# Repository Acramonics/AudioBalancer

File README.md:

AudioBalancer
=============

Andrew Martin, acramonics, 2026
-------------------------------

`AudioBalancer` is a balanced line receiver to unbalanced and an
unbalanced to balanced driver on a single board. This could be used as
a standalone device or as an add on to another circuit - the board has
been designed to be as small as possible while using through-hole
components.

A -15V/0/+15V power supply is needed.

The circuit uses the SSM2141P receiver and SSM2142P receiver. These
are now end-of-life, but still quite easy to find quite cheaply.

Both receiver and driver contain capacitors for decoupling 48V phantom
power on the balanced connection protection for the chips if these are
charged and the inputs are accidentally shorted to earth. See the
[Phantom Menace](./docs/AES5335_48V_Phantom_Menace.pdf) document.

|    | Components               | Value | Function            | Options              |
| :- | :----------------------- | :---- | :------------------ | :------------------- |
| 1  | C3,C4,C13,C14            | 10nF  | HF coupling         | Omit if not needed   |
| 2  | C1,C2,C11,C12            | 47uF  | Phantom protection  | Bridge if not needed |
| 3  | D1,D2,D3,D4,D5,D6,D7,D8  | SB160 | Short protection    | Omit if not needed   |
| 4  | R4,R5,R6,R7              | 10K   | Short protection    | Omit if not needed   |

1. The 10nF capacitors across the decoupling capacitors are to ensure
   a good high frequency response. Depending on your application these
   may not be needed.

2. These prevent the 48V phantom power reaching the ICs. If you are
   confident that this is not a problem in your application, they may
   be bridged out.

3. If the 47uF capacitors are charged by phantom power and the signal
   pins are accidentally shorted to ground these provide protection to
   the chips by shunting the voltage to the power rail. Normal 1N4148
   diodes may also be used, but they will not provide the same degree
   of protection.

4. These allow the 47uF capacitors to discharge in the event of a short.

Consequently, if you are confident of no problems with phantom power,
you can omit the eight Schottky diodes, and the four 10K resistors and
replace the four 47uF coupling capacitors with links.

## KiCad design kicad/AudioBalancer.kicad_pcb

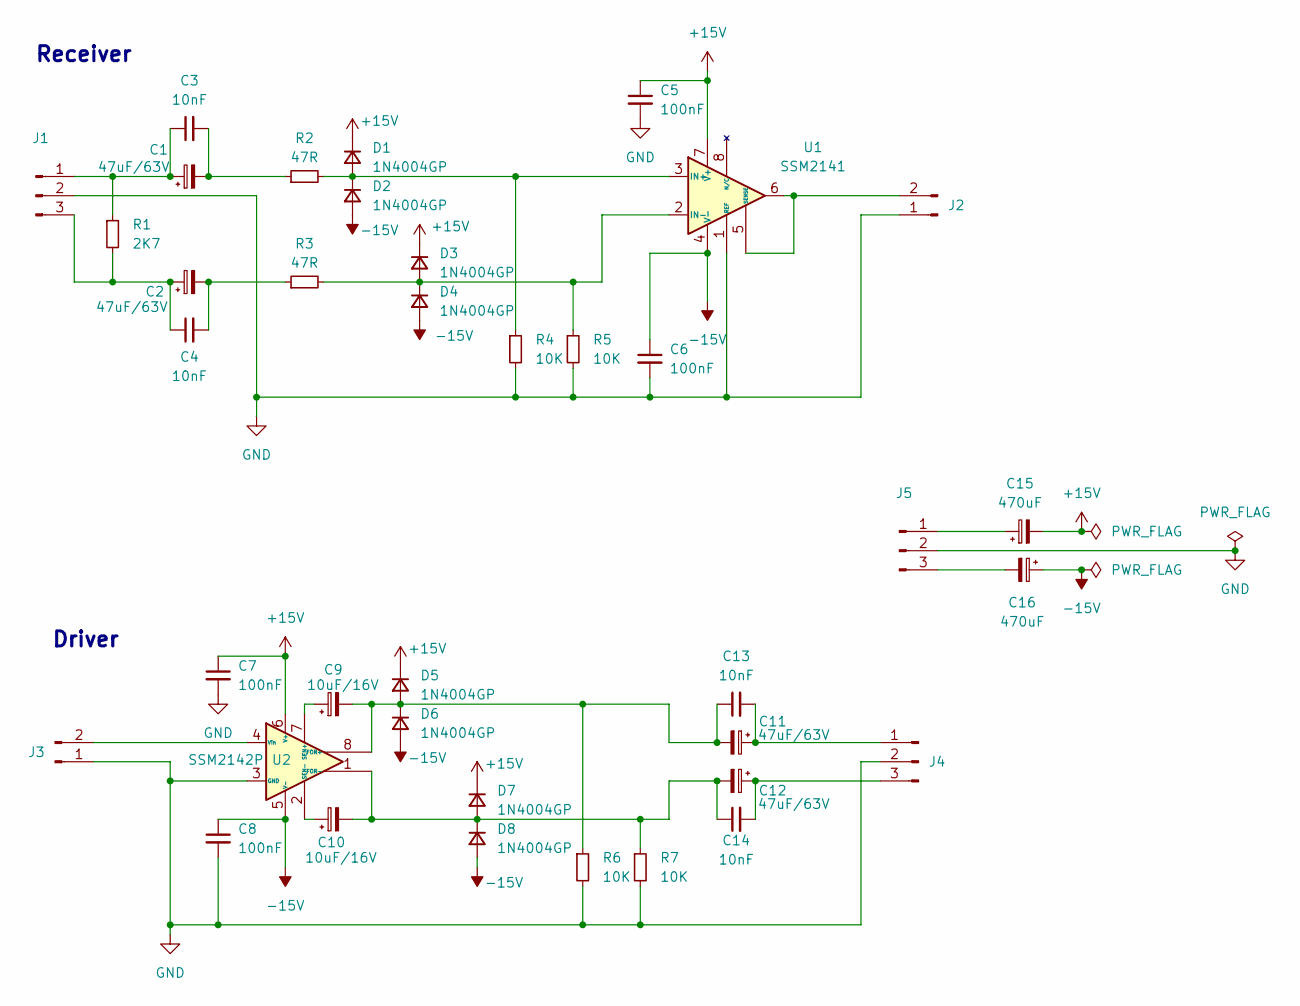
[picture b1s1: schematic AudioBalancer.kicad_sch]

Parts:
C1, C2, C11, C12: 47uF/63V; CP_Radial_D10.0mm_P5.00mm
C3, C4, C13, C14: 10nF; C_Rect_L7.0mm_W2.0mm_P5.00mm
C5, C6, C7, C8: 100nF; C_Rect_L7.0mm_W2.5mm_P5.00mm
C9, C10: 10uF/16V; CP_Radial_D5.0mm_P2.00mm
C15, C16: 470uF; CP_Radial_D10.0mm_P5.00mm_P7.50mm
D1, D2, D3, D4, D5, D6, D7, D8: 1N4004GP; D_DO-41_SOD81_P10.16mm_Horizontal
J1, J4, J5: Conn_01x03_Pin; Molex_KK-254_AE-6410-03A_1x03_P2.54mm_Vertical
J2, J3: Conn_01x02_Pin; Molex_KK-254_AE-6410-02A_1x02_P2.54mm_Vertical
R1: 2K7; R_Axial_DIN0207_L6.3mm_D2.5mm_P10.16mm_Horizontal
R2, R3: 47R; R_Axial_DIN0207_L6.3mm_D2.5mm_P10.16mm_Horizontal
R4, R5, R6, R7: 10K; R_Axial_DIN0207_L6.3mm_D2.5mm_P10.16mm_Horizontal
U1: SSM2141; DIP-8_W7.62mm
U2: SSM2142P; DIP-8_W7.62mm

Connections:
+15V: C5.1, C7.1, C15.2, D1.1 (K), D3.1 (K), D5.1 (K), D7.1 (K), U1.7 (V+), U2.6 (V+)
-15V: C6.1, C8.1, C16.1, D2.2 (A), D4.2 (A), D6.2 (A), D8.2 (A), U1.4 (V-), U2.5 (V-)
GND: C5.2, C6.2, C7.2, C8.2, J1.2, J2.1, J3.1, J4.2, J5.2, R4.2, R5.2, R6.2, R7.2, U1.1 (REF), U2.3 (GND)
unnamed: C1.2, C3.2, R2.1
unnamed: C2.2, C4.2, R3.1
unnamed: D1.2 (A), D2.1 (K), R2.2, R4.1, U1.3 (IN+)
unnamed: D3.2 (A), D4.1 (K), R3.2, R5.1, U1.2 (IN-)
unnamed: C9.2, C11.2, C13.1, D5.2 (A), D6.1 (K), R6.1, U2.8 (FOR+)
unnamed: C10.2, C12.2, C14.1, D7.2 (A), D8.1 (K), R7.1, U2.1 (FOR-)
unnamed: C1.1, C3.1, J1.1, R1.1
unnamed: C2.1, C4.1, J1.3, R1.2
unnamed: J2.2, U1.5 (SENSE), U1.6
unnamed: J3.2, U2.4 (Vin)
unnamed: C11.1, C13.2, J4.1
unnamed: C12.1, C14.2, J4.3
unnamed: C15.1, J5.1
unnamed: C16.2, J5.3
unnamed: C9.1, U2.7 (SEN+)
unnamed: C10.1, U2.2 (SEN-)

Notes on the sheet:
Receiver
Driver

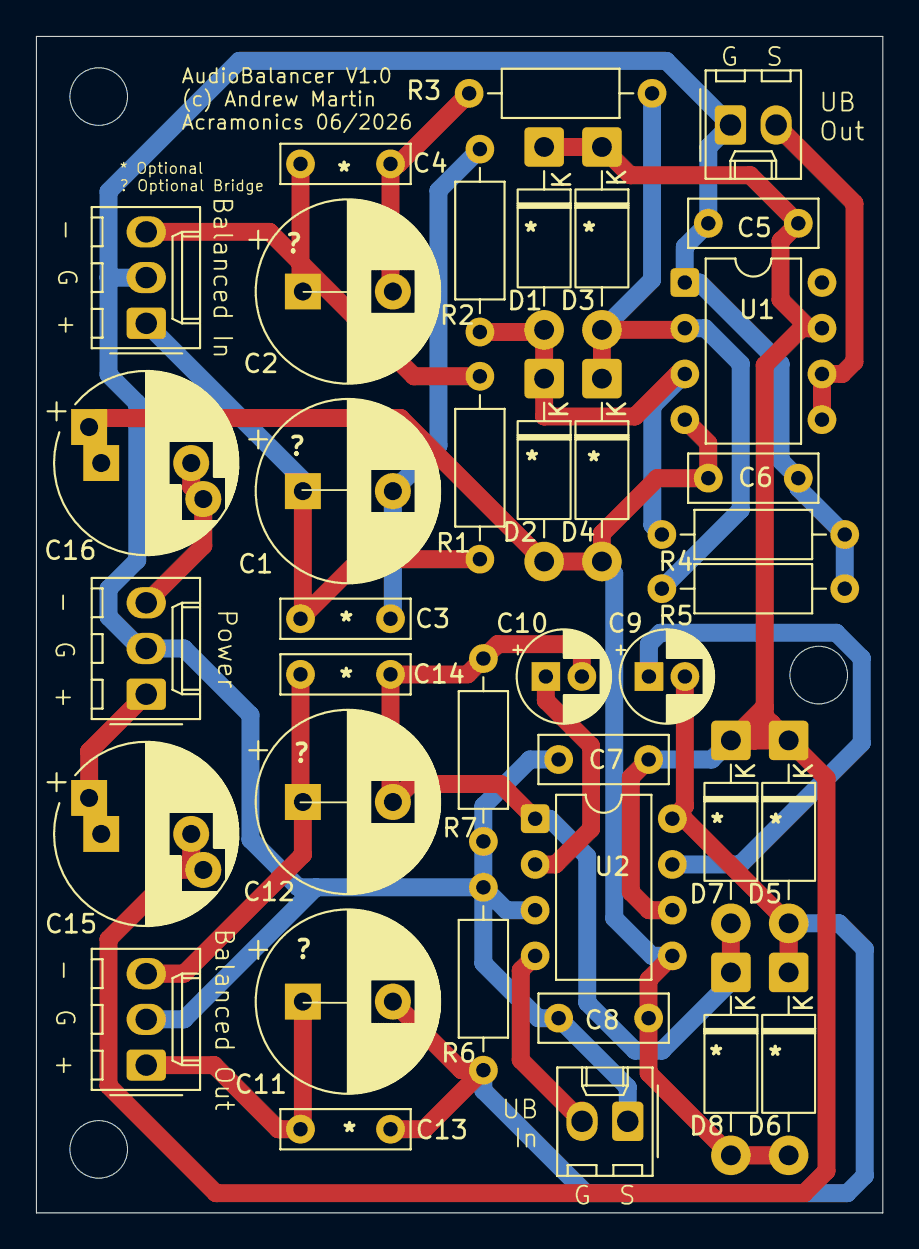
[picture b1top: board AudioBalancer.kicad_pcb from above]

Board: 2 copper layers, 47.0 x 65.4 mm, 38 parts (0 on the bottom side), 19 nets.

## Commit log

2026-06-10 First draft
2026-06-11 Added ppaers on phantom power problems
2026-06-12 Completed V1.0
2026-06-12 Added readme
2026-06-14 Changed to protection values in 'The 48 Volt Phantom Menace Returns'
2026-06-23 Added BOM
2026-06-29 Added schematic pdf
